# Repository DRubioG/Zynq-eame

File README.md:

# Introducción / Introduction

**[ES]** Este es el repositorio en GitHub del blog [soceame.wordpress.com](http://soceame.wordpress.com) en el que se colgará toda la información sobre cómo construir SoCs de Xilinx 

**[EN]** This is the GitHub's repository of the [soceame.wordpress.com](https://soceame.wordpress.com)'s blog where it will be uploaded all information about how to build Xilinx's SoCs

# Contenido / Content

- [Documentación/Documentation](/Documentacion): 

**[ES]** En esta carpeta se ubicarán los documentos que explican la construcción de los SoCs 

**[EN]** In this folder will be placed the documents which explaining how to build the SoCs

- [Zynq-eame_0](/Zynq-eame_0): ❗ No terminada / Unfinished ❗

**[ES]** Esta carpeta contiene los esquemáticos de la Zynq-eame_0 en pdf y en KiCad.

Esta placa está construida a partir de un XC7Z010-CLG400.

**[EN]** This folder contains the Zynq-eame_0' schematics in pdf and in KiCad.

This board is built from a XC7Z010-CLG400.

- [Zynq-eame_UltraScale_0](/Zynq-eame_UltraScale_0): ❗ Inicio / Started ❗

**[ES]** Esta carpeta contiene los esquemáticos de la Zynq-eame_UltraScale_0 en pdf y en KiCad.

Esta placa está construida a partir de un XCZU2CG-SBVA484.

**[EN]** This folder contains the Zynq-eame_UltraScale_0' schematics in pdf and in KiCad.

This board is built from a XCZU2CG-SBVA484.

**[ES]** Estos son proyectos Open Hardware 

**[EN]** These are Open Hardware projects

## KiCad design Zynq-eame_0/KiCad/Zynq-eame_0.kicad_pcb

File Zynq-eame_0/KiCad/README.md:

# FPGA_propia
 En este repositorio se subirán los ficheros que permitirán crear una FPGA basada en Zynq-7000

Todo el desarrollo está hecho con KiCad (software libre) para que cualquiera pueda replicarla o mejorarla a su gusto con los ficheros que se van a publicar

## Libreria
El fichero tiene una librería llamada 'Zynq-7000' en la que está el symbol de un XC7Z010 del cual se implementará la versión CLG400 (400 pines en formato de soldadura BGA) 
## XC7Z010-BUENO
El símbolo consta de 9 partes, de las que se va a describir su selección a continuación
### - _Símbolo A_

En este símbolo se reflejan los pines de referencia, además de los pines de depuración TMS, TCK, TDI y TDO. Estos pines pueden necesitar de un cable depurar para cargar el programa o de un USB OTG, que permita evitar tener que usar un cable depurador.

### - _Símbolo B_

En este símbolo se reflejan los pines que no tienen conexión

### - _Símbolo c_

En este símbolo se reflejan los pines de entrada/salida que se podrán configurar como se quiera

### - _Símbolo D_

En este símbolo se reflejan los pines de entrada/salida que se podrán configurar como se quiera

### - _Símbolo E_

En este símbolo se reflejan los pines que van a ir a la/las memoria ram. A los pines de la ram se pueden unir varias memorias para aumentar su tamaño.

### - _Símbolo F_

En este símbolo se reflejan los pines MIO

### - _Símbolo G_

En este símbolo se reflejan los pines MIO continuación de los anteriores

### - _Símbolo H_

En este símbolo se reflejan las alimentaciones de cada parte del integrado. Hay que tener en cuenta que cada parte tiene una alimentación distinta, la VCCO_BRAM y los VCCO_PINT de 1V, los VCCO_MIO 3.3V, los VCCO_DDR de 1.35V y los VCCAUX y los VCCPAUX de 1.8V

### - _Símbolo I_

En este símbolo se reflejan las masas de todo el integrado. Todas las masas van unidas a mismo punto.

### - *Formato del integrado*

En esta imagen se refleja como es el integrado CLG400 de 400 pines(20x20) para BGA

*** Toda la documentación del frabicante se puede obtener del siguiente enlace: ***
Documentación para el empaquetado: https://www.xilinx.com/support/documentation/user_guides/ug865-Zynq-7000-Pkg-Pinout.pdf
Documentación de los pines: https://www.xilinx.com/support/packagefiles/z7packages/xc7z010clg400pkg.txt

## Memoria RAM
Para la memoria ram se utiliza una MT4K256M16TW-107:P
### Datasheet
http://www.farnell.com/datasheets/3151560.pdf
### Símbolo
El símbolo utilizado es el siguiente

### Huella
La huella de la memoria ram consta de una matriz de 6x16 que está fragmetada en dos partes separadas por una zona en la que van 3 columnas de pines vacías.

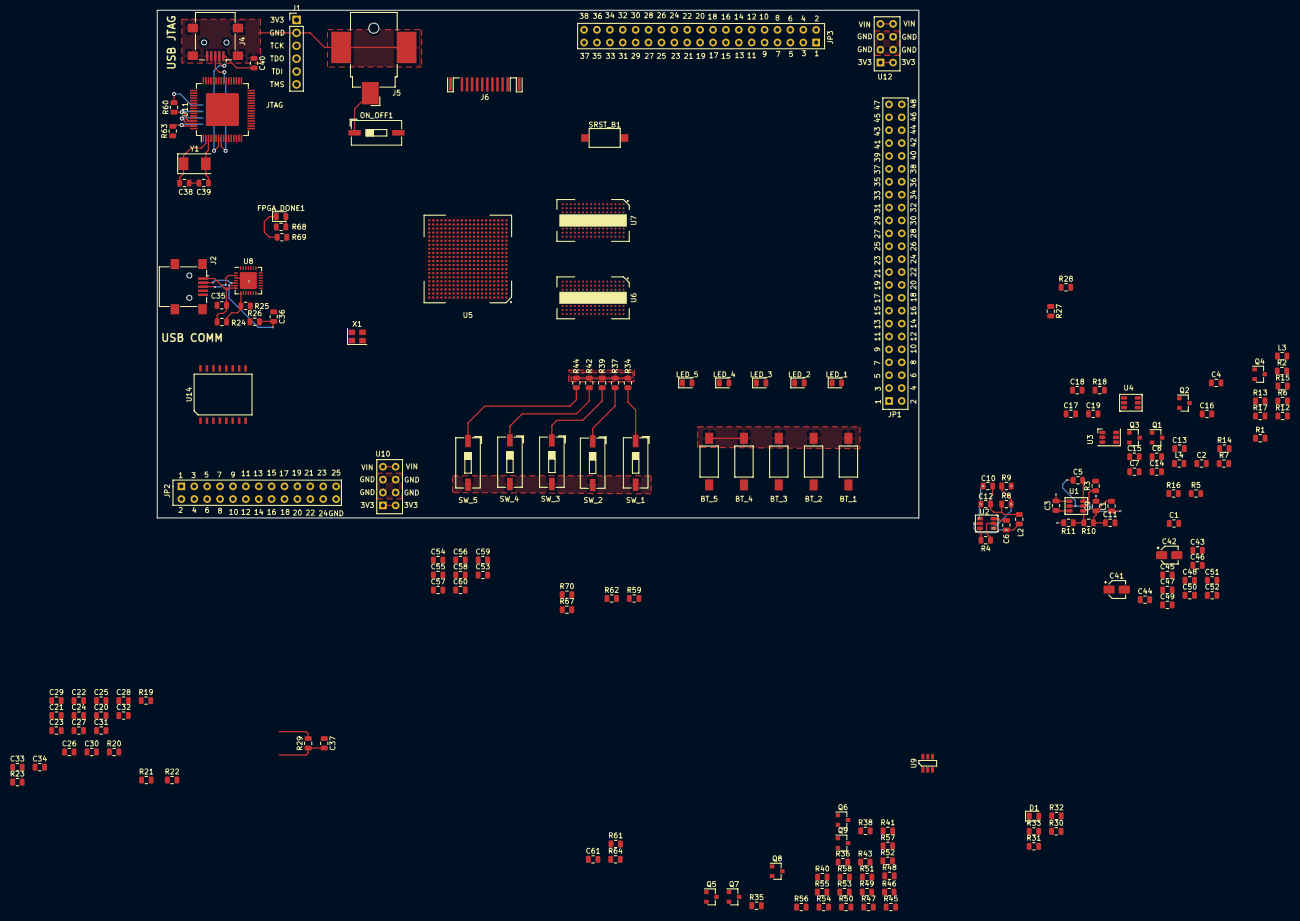
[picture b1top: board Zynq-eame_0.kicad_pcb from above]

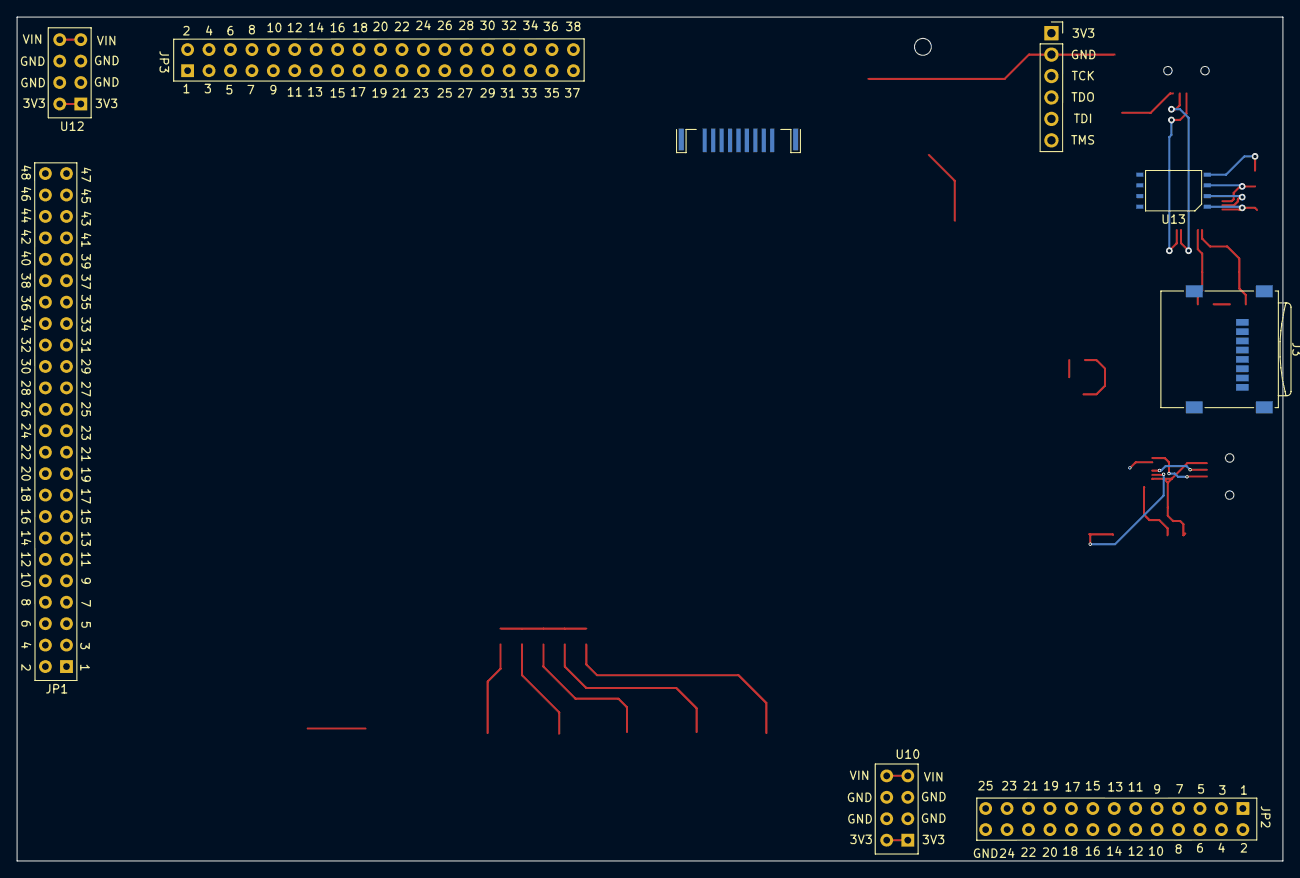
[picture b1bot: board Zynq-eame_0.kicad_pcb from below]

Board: 4 copper layers, 150.0 x 100.0 mm, 186 parts (2 on the bottom side), 302 nets.

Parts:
BT_1, BT_2, BT_3, BT_4, BT_5: SW_Push; SW_SPST_FSMSM
C1, C2, C3, C4, C9, C10, C11, C12, C13, C14, C15, C16: 10uF; C_0805_2012Metric
C5, C6, C7, C8, C17, C18, C19, C20, C21, C22, C23, C24, C25, C26, C27, C28, C29, C30, C31, C32, C33, C34, C37, C40, C43, C44, C53, C54, C55, C56, C57, C58, C59, C60, C61: 100nF; C_0805_2012Metric
C35: 4.7uF; R_0805_2012Metric
C36: 100nF; R_0805_2012Metric
C38, C39: 27pF; C_0805_2012Metric
C41, C42: 4.7uF; CP_Elec_3x5.4
C45: 3.3uF; C_0805_2012Metric
C46, C47, C48, C49, C50, C51, C52: C; C_0805_2012Metric
D1: LED_ALT; D_0805_2012Metric
FPGA_DONE1: LED_ALT; LED_0805_2012Metric
J1: Conn_01x06; PinHeader_1x06_P2.54mm_Vertical
J2, J4: USB_B_Micro; USB_Mini-B_Lumberg_2486_01_Horizontal
J3: Micro_SD_Card; microSD_HC_Wuerth_693072010801
J5: Barrel_Jack; BarrelJack_CUI_PJ-036AH-SMT_Horizontal
J6: HDMI_A; HDMI_A_Contact_Technology_HDMI-19APL2_Horizontal
JP1: PINES_48
JP2: PIN_25; PINES_40
JP3: PINES_38
L1, L2, L3, L4: 4.7uH; L_0805_2012Metric
LED_1, LED_2, LED_3, LED_4, LED_5: LED_ALT; LED_0805_2012Metric
ON_OFF1: SW_SPST; SW_DIP_SPSTx01_Slide_9.78x4.72mm_W8.61mm_P2.54mm
Q1, Q2, Q3, Q4: MMBT3904; SOT-23
Q5, Q6, Q7, Q8, Q9: MMBF170; SOT-23
R1, R2, R4, R5, R6, R7, R25, R36, R41, R46, R51, R56: 10k; R_0805_2012Metric
R3, R16, R17: 0R; R_0805_2012Metric
R8, R12: 33k; R_0805_2012Metric
R9, R11, R13, R14: 100k; R_0805_2012Metric
R10: 79k; R_0805_2012Metric
R15: 75k; R_0805_2012Metric
R18, R23: 240R 1%; R_0805_2012Metric
R19, R20, R21, R22: 1k 1%; R_0805_2012Metric
R24, R29: 4.7k; R_0805_2012Metric
R26, R35, R40, R45, R50, R55: 1k; R_0805_2012Metric
R27, R28, R34, R37, R39, R42, R44, R47, R49, R52, R54, R57, R67: 4.7K; R_0805_2012Metric
R30: 820; R_0805_2012Metric
R31: 1300; R_0805_2012Metric
R32, R64, R68, R69: 1K; R_0805_2012Metric
R33, R59, R62, R63: 10K; R_0805_2012Metric
R38, R43, R48, R53, R58: 261; R_0805_2012Metric
R60: 2K2; R_0805_2012Metric
R61: 12K; R_0805_2012Metric
R70: 330; R_0805_2012Metric
SRST_B1: SW_Push; SW_SPST_CK_RS282G05A3
SW_1, SW_2, SW_3, SW_4, SW_5: SW_SPST; SW_DIP_SPSTx01_Slide_9.78x4.72mm_W8.61mm_P2.54mm
U1, U2, U3, U4: TPS563201
U5: XC7Z010-BUENO; BGA-400_20x20_17.0x17.0mm
U6, U7: MT41K256M16TW-107_P; BGA-144_9x16_8.0x14.0mm
U8: CP2102N-A01-GQFN28; QFN-28-1EP_5x5mm_P0.5mm_EP3.35x3.35mm
U9: TPS3106K33DBV; SOT-23
U10, U12: PINES_ALIMENTACION; PINES_40
U11: FT2232H; LQFP-64-1EP_10x10mm_P0.5mm_EP6.5x6.5mm
U13: 93C46; EIAJ_SOIC
U14: S25FL128S; S03016-(SOIC-16)
X1: ASE-33.333MHz; Oscillator_SMD_Abracon_ASE-4Pin_3.2x2.5mm
Y1: 12MHz; Crystal_SMD_0603-2Pin_6.0x3.5mm

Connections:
+1V0: C10.1, C12.1, L2.2, Q2.1, R8.1, R30.1, U5.G7, U5.G11, U5.G13, U5.H10, U5.H12, U5.J7, U5.J13, U5.K12, U5.L7, U5.L13, U5.M12, U5.N7, U5.N13, U5.P8, U5.P12, U5.R7, U5.R13
+1V8: C14.1, C16.1, C45.1, C46.1, C47.1, C48.1, C49.1, C50.1, C51.1, C52.1, L4.2, R3.2, R14.1, U5.F8, U5.F11, U5.G8, U5.G9, U5.H8, U5.J9, U5.J11, U5.K8, U5.L11, U5.M8, U5.N9, U5.N11, U5.P10, U5.R9, U11.12, U11.37, U11.49, U11.64
+1V35: C9.1, C11.1, C20.1, C21.1, C23.1, C24.1, C25.1, C26.1, C27.1, C28.1, C29.1, C30.1, C53.1, C54.1, C55.1, C56.1, C57.1, C58.1, C59.1, L1.2, R1.2, R10.1, R19.1, U5.A3, U5.D2, U5.E5, U5.G1, U5.H4, U5.L3, U5.P2, U5.R5, U5.U1, U5.V4, U6.A1, U6.A8, U6.B2, U6.C1, U6.C9, U6.D2, U6.D9, U6.E9, U6.F1, U6.G7, U6.H2, U6.H9, U6.K2, U6.K8, U6.N1, U6.N9, U6.R1, U6.R9, U7.A1, U7.A8, U7.B2, U7.C1, U7.C9, U7.D2, U7.D9, U7.E9, U7.F1, U7.G7, U7.H2, U7.H9, U7.K2, U7.K8, U7.N1, U7.N9, U7.R1, U7.R9
+3V3: BT_1.2, BT_2.2, BT_3.2, BT_4.2, BT_5.2, C13.1, C15.1, C37.2, C61.1, J1.1, J3.4, L3.2, LED_1.2, LED_2.2, LED_3.2, LED_4.2, LED_5.2, R12.1, R16.1, R17.1, R27.1, R28.1, R29.1, R32.2, R33.1, R34.1, R37.1, R39.1, R42.1, R44.1, R59.1, R62.1, R63.1, R64.1, R67.1, R68.1, R70.1, U5.A13, U5.B6, U5.B16, U5.C19, U5.D7, U5.D12, U5.E15, U5.F18, U5.H14, U5.J17, U5.K6, U5.K20, U5.M6, U5.M16, U5.N6, U5.R6, U5.T6, U5.T8, U5.U11, U5.W7, U5.Y10, U9.6, U10.1, U10.2, U11.20, U11.31, U11.42, U11.50, U11.56, U12.1, U12.2, U13.6, U13.8, U14.2, X1.4
+5V: J5.1, ON_OFF1.1
/Entradas y Salidas/BANK34_N17: JP1.42, U5.N17
/Entradas y Salidas/BANK34_N18: JP1.2, U5.N18
/Entradas y Salidas/BANK34_N20: JP1.6, U5.N20
/Entradas y Salidas/BANK34_P14: JP1.21, U5.P14
/Entradas y Salidas/BANK34_P15: JP1.46, U5.P15
/Entradas y Salidas/BANK34_P16: JP1.48, U5.P16
/Entradas y Salidas/BANK34_P18: JP1.44, U5.P18
/Entradas y Salidas/BANK34_P19: JP1.4, U5.P19
/Entradas y Salidas/BANK34_P20: JP1.8, U5.P20
/Entradas y Salidas/BANK34_R14: JP1.23, U5.R14
/Entradas y Salidas/BANK34_R16: JP1.26, U5.R16
/Entradas y Salidas/BANK34_R17: JP1.28, U5.R17
/Entradas y Salidas/BANK34_R18: JP1.32, U5.R18
/Entradas y Salidas/BANK34_R19: JP1.1, U5.R19
/Entradas y Salidas/BANK34_T10: JP1.5, U5.T10
/Entradas y Salidas/BANK34_T11: JP1.3, U5.T11
/Entradas y Salidas/BANK34_T12: JP1.7, U5.T12
/Entradas y Salidas/BANK34_T14: JP1.17, U5.T14
/Entradas y Salidas/BANK34_T15: JP1.19, U5.T15
/Entradas y Salidas/BANK34_T16: JP1.33, U5.T16
/Entradas y Salidas/BANK34_T17: JP1.30, U5.T17
/Entradas y Salidas/BANK34_T20: JP1.10, U5.T20
/Entradas y Salidas/BANK34_U12: JP1.9, U5.U12
/Entradas y Salidas/BANK34_U14: JP1.41, U5.U14
/Entradas y Salidas/BANK34_U15: JP1.43, U5.U15
/Entradas y Salidas/BANK34_U17: JP1.35, U5.U17
/Entradas y Salidas/BANK34_U18: JP1.45, U5.U18
/Entradas y Salidas/BANK34_U19: JP1.47, U5.U19
/Entradas y Salidas/BANK34_U20: JP1.12, U5.U20
/Entradas y Salidas/BANK34_V12: JP1.13, U5.V12
/Entradas y Salidas/BANK34_V13: JP1.11, U5.V13
/Entradas y Salidas/BANK34_V15: JP1.37, U5.V15
/Entradas y Salidas/BANK34_V16: JP1.22, U5.V16
/Entradas y Salidas/BANK34_V17: JP1.34, U5.V17
/Entradas y Salidas/BANK34_V18: JP1.36, U5.V18
/Entradas y Salidas/BANK34_V20: JP1.14, U5.V20
/Entradas y Salidas/BANK34_W13: JP1.15, U5.W13
/Entradas y Salidas/BANK34_W14: JP1.29, U5.W14
/Entradas y Salidas/BANK34_W15: JP1.39, U5.W15
/Entradas y Salidas/BANK34_W16: JP1.24, U5.W16
/Entradas y Salidas/BANK34_W18: JP1.38, U5.W18
/Entradas y Salidas/BANK34_W19: JP1.40, U5.W19
/Entradas y Salidas/BANK34_W20: JP1.16, U5.W20
/Entradas y Salidas/BANK34_Y14: JP1.31, U5.Y14
/Entradas y Salidas/BANK34_Y16: JP1.25, U5.Y16
/Entradas y Salidas/BANK34_Y17: JP1.27, U5.Y17
/Entradas y Salidas/BANK34_Y18: JP1.18, U5.Y18
/Entradas y Salidas/BANK34_Y19: JP1.20, U5.Y19
/Entradas y Salidas/BANK35_F16: JP2.3, U5.F16
/Entradas y Salidas/BANK35_F17: JP2.5, U5.F17
/Entradas y Salidas/BANK35_G14: JP2.1, U5.G14
/Entradas y Salidas/BANK35_G15: JP2.18, U5.G15
/Entradas y Salidas/BANK35_G19: JP2.12, U5.G19
/Entradas y Salidas/BANK35_G20: JP2.14, U5.G20
/Entradas y Salidas/BANK35_H15: JP2.16, U5.H15
/Entradas y Salidas/BANK35_H20: JP2.10, U5.H20
/Entradas y Salidas/BANK35_J14: JP2.22, U5.J14
/Entradas y Salidas/BANK35_J15: JP2.6, U5.J15
/Entradas y Salidas/BANK35_J16: JP2.4, U5.J16
/Entradas y Salidas/BANK35_J20: JP2.8, U5.J20
/Entradas y Salidas/BANK35_K14: JP2.20, U5.K14
/Entradas y Salidas/BANK35_K16: JP2.2, U5.K16
/Entradas y Salidas/BANK35_L14: JP2.23, U5.L14
/Entradas y Salidas/BANK35_L15: JP2.21, U5.L15
/Entradas y Salidas/BANK35_L19: JP2.15, U5.L19
/Entradas y Salidas/BANK35_M14: JP2.19, U5.M14
/Entradas y Salidas/BANK35_M15: JP2.17, U5.M15
/Entradas y Salidas/BANK35_M17: JP2.11, U5.M17
/Entradas y Salidas/BANK35_M18: JP2.13, U5.M18
/Entradas y Salidas/BANK35_M19: JP2.7, U5.M19
/Entradas y Salidas/BANK35_M20: JP2.9, U5.M20
/Entradas y Salidas/BANK35_N15: JP2.24, U5.N15
/Entradas y Salidas/BANK35_N16: JP2.25, U5.N16
/Entradas y Salidas/BT_1: BT_1.1, R47.2, U5.H18
/Entradas y Salidas/BT_2: BT_2.1, R49.2, U5.F19
/Entradas y Salidas/BT_3: BT_3.1, R52.2, U5.F20
/Entradas y Salidas/BT_4: BT_4.1, R54.2, U5.G17
/Entradas y Salidas/BT_5: BT_5.1, R57.2, U5.G18
/Entradas y Salidas/HDMI_CLK+: J6.10, U5.B19
/Entradas y Salidas/HDMI_CLK-: J6.12, U5.A20
/Entradas y Salidas/HDMI_D0+: J6.7, U5.E17
/Entradas y Salidas/HDMI_D0-: J6.9, U5.D18
/Entradas y Salidas/HDMI_D1+: J6.4, U5.D19
/Entradas y Salidas/HDMI_D1-: J6.6, U5.D20
/Entradas y Salidas/HDMI_D2+: J6.1, U5.E18
/Entradas y Salidas/HDMI_D2-: J6.3, U5.E19
/Entradas y Salidas/LED_1: R35.1, U5.L20
/Entradas y Salidas/LED_2: R40.1, U5.K19
/Entradas y Salidas/LED_3: R45.1, U5.J19
/Entradas y Salidas/LED_4: R50.1, U5.L16
/Entradas y Salidas/LED_5: R55.1, U5.L17
/Entradas y Salidas/SW_1: R34.2, SW_1.1, U5.K17
/Entradas y Salidas/SW_2: R37.2, SW_2.1, U5.K18
/Entradas y Salidas/SW_3: R39.2, SW_3.1, U5.H16
/Entradas y Salidas/SW_4: R42.2, SW_4.1, U5.H17
/Entradas y Salidas/SW_5: R44.2, SW_5.1, U5.J18
/Memoria RAM/DDR_A0: U5.N2, U6.N3, U7.N3
/Memoria RAM/DDR_A1: U5.K2, U6.P7, U7.P7
/Memoria RAM/DDR_A2: U5.M3, U6.P3, U7.P3
/Memoria RAM/DDR_A3: U5.K3, U6.N2, U7.N2
/Memoria RAM/DDR_A4: U5.M4, U6.P8, U7.P8
/Memoria RAM/DDR_A5: U5.L1, U6.P2, U7.P2
/Memoria RAM/DDR_A6: U5.L4, U6.R8, U7.R8
/Memoria RAM/DDR_A7: U5.K4, U6.R2, U7.R2
/Memoria RAM/DDR_A8: U5.K1, U6.T8, U7.T8
/Memoria RAM/DDR_A9: U5.J4, U6.R3, U7.R3
/Memoria RAM/DDR_A10: U5.F5, U6.L7, U7.L7
/Memoria RAM/DDR_A11: U5.G4, U6.R7, U7.R7
/Memoria RAM/DDR_A12: U5.E4, U6.N7, U7.N7
/Memoria RAM/DDR_A13: U5.D4, U6.T3, U7.T3
/Memoria RAM/DDR_A14: U5.F4, U6.T7, U7.T7
/Memoria RAM/DDR_BA0: U5.L5, U6.M2, U7.M2
/Memoria RAM/DDR_BA1: U5.R4, U6.N8, U7.N8
/Memoria RAM/DDR_BA2: U5.J5, U6.M3, U7.M3
/Memoria RAM/DDR_CAS: U5.P5, U6.K3, U7.K3
/Memoria RAM/DDR_CKE: U5.N3, U6.K9, U7.K9
/Memoria RAM/DDR_CLK+: R21.1, U5.L2, U6.J7, U7.J7
/Memoria RAM/DDR_CLK-: R21.2, U5.M2, U6.K7, U7.K7
/Memoria RAM/DDR_CS: U5.N1, U6.L2, U7.L2
/Memoria RAM/DDR_D0: U5.C3, U6.E3
/Memoria RAM/DDR_D1: U5.B3, U6.F7
/Memoria RAM/DDR_D2: U5.A2, U6.F2, U6.F8
/Memoria RAM/DDR_D4: U5.D3, U6.H3
/Memoria RAM/DDR_D5: U5.D1, U6.H8
/Memoria RAM/DDR_D6: U5.C1, U6.G2
/Memoria RAM/DDR_D7: U5.E1, U6.H7
/Memoria RAM/DDR_D8: U5.E2, U6.D7
/Memoria RAM/DDR_D9: U5.E3, U6.C3
/Memoria RAM/DDR_D10: U5.G3, U6.C8
/Memoria RAM/DDR_D11: U5.H3, U6.C2
/Memoria RAM/DDR_D12: U5.J3, U6.A7
/Memoria RAM/DDR_D13: U5.H2, U6.A2
/Memoria RAM/DDR_D14: U5.H1, U6.B8
/Memoria RAM/DDR_D15: U5.J1, U6.A3
/Memoria RAM/DDR_D16: U5.P1, U7.E3
/Memoria RAM/DDR_D17: U5.P3, U7.F7
/Memoria RAM/DDR_D18: U5.R3, U7.F2
/Memoria RAM/DDR_D19: U5.R1, U7.F8
/Memoria RAM/DDR_D20: U5.T4, U7.H3
/Memoria RAM/DDR_D21: U5.U4, U7.H8
/Memoria RAM/DDR_D22: U5.U2, U7.G2
/Memoria RAM/DDR_D23: U5.U3, U7.H7
/Memoria RAM/DDR_D24: U5.V1, U7.D7
/Memoria RAM/DDR_D25: U5.Y3, U7.C3
/Memoria RAM/DDR_D26: U5.W1, U7.C8
/Memoria RAM/DDR_D27: U5.Y4, U7.C2
/Memoria RAM/DDR_D28: U5.Y2, U7.A7
/Memoria RAM/DDR_D29: U5.W3, U7.A2
/Memoria RAM/DDR_D30: U5.V2, U7.B8
/Memoria RAM/DDR_D31: U5.V3, U7.A3
/Memoria RAM/DDR_DQM0: U5.A1, U6.E7
/Memoria RAM/DDR_DQM1: U5.F1, U6.D3
/Memoria RAM/DDR_DQM2: U5.T1, U7.E7
/Memoria RAM/DDR_DQM3: U5.Y1, U7.D3
/Memoria RAM/DDR_DQS0+: U5.C2, U6.F3
/Memoria RAM/DDR_DQS0-: U5.B2, U6.G3
/Memoria RAM/DDR_DQS1+: U5.G2, U6.C7
/Memoria RAM/DDR_DQS1-: U5.F2, U6.B7
/Memoria RAM/DDR_DQS2+: U5.R2, U7.F3
/Memoria RAM/DDR_DQS2-: U5.T2, U7.G3
/Memoria RAM/DDR_DQS3+: U5.W5, U7.C7
/Memoria RAM/DDR_DQS3-: U5.W4, U7.B7
/Memoria RAM/DDR_ODT: U5.N5, U6.K1, U7.K1
/Memoria RAM/DDR_RAS: U5.P4, U6.J3, U7.J3
/Memoria RAM/DDR_RESETN: R22.1, U5.B4, U6.T2, U7.T2
/Memoria RAM/DDR_VREF: C17.1, C21.2, C22.1, R19.2, R20.1, U5.H6, U5.P6
/Memoria RAM/DDR_WE: U6.L3, U7.L3
/Referencias y MIOs/EECLK: R62.2, U11.62, U13.2
/Referencias y MIOs/EECS: R63.2, U11.63, U13.1
/Referencias y MIOs/EEDATA: R60.1, U11.61, U13.3
/Referencias y MIOs/FPGA_DONE: FPGA_DONE1.2, R68.2, U5.R11
/Referencias y MIOs/MIO1: R70.2, U5.A7, U14.7
/Referencias y MIOs/MIO2: U5.B8, U14.15
/Referencias y MIOs/MIO3: U5.D6, U14.8
/Referencias y MIOs/MIO4: U5.B7, U14.9
/Referencias y MIOs/MIO5: U5.A6, U14.1
/Referencias y MIOs/MIO6: U5.A5, U14.16
/Referencias y MIOs/PS_CLK: U5.E7, X1.3
/Referencias y MIOs/RX(MIO24): U5.A16, U8.26
/Referencias y MIOs/SD_CLK: J3.5, U5.D14
/Referencias y MIOs/SD_CMD: J3.3, U5.C17
/Referencias y MIOs/SD_D0: J3.7, U5.E12
/Referencias y MIOs/SD_D1: J3.8, U5.A9
/Referencias y MIOs/SD_D2: J3.1, U5.F13
/Referencias y MIOs/SD_D3: J3.2, U5.B15
/Referencias y MIOs/SRST_B: R67.2, SRST_B1.1, U5.B10
/Referencias y MIOs/TCK: J1.3, U5.F9, U11.16
/Referencias y MIOs/TDI: J1.5, U5.G6, U11.17
/Referencias y MIOs/TDO: J1.4, U5.F6, U11.18
/Referencias y MIOs/TMS: J1.6, U5.J6, U11.19
/Referencias y MIOs/TX(MIO25): U5.F15, U8.25
GND: C1.2, C2.2, C3.2, C4.2, C9.2, C10.2, C11.2, C12.2, C13.2, C14.2, C15.2, C16.2, C17.2, C18.2, C19.2, C20.2, C22.2, C23.2, C24.2, C25.2, C26.2, C27.2, C28.2, C29.2, C30.2, C31.2, C32.2, C33.2, C34.2, C35.1, C36.1, C37.1, C38.2, C39.2, C40.1, C41.2, C42.2, C43.2, C44.2, C45.2, C46.2, C47.2, C48.2, C49.2, C50.2, C51.2, C52.2, C53.2, C54.2, C55.2, C56.2, C57.2, C58.2, C59.2, C61.2, D1.1, J1.2, J2.5, J2.6, J3.6, J3.9, J4.5, J4.6, J5.2, J6.2, J6.5, J6.8, J6.11, J6.17, J6.SH, JP2.26, Q1.2, Q2.2, Q3.2, Q4.2, Q5.2, Q6.2, Q7.2, Q8.2, Q9.2, R9.2, R11.2, R13.2, R15.2, R18.2, R20.2, R22.2, R23.2, R25.2, R31.2, R36.2, R41.2, R46.2, R47.1, R49.1, R51.2, R52.1, R54.1, R56.2, R57.1, R61.1, R69.2, SRST_B1.2, SW_1.2, SW_2.2, SW_3.2, SW_4.2, SW_5.2, U1.1, U2.1, U3.1, U4.1, U5.A8, U5.A18, U5.B1, U5.B11, U5.C4, U5.C9, U5.C14, U5.D17, U5.E10, U5.E20, U5.F3, U5.F7, U5.F10, U5.G10, U5.G12, U5.G16, U5.H7, U5.H9, U5.H11, U5.H13, U5.H19, U5.J2, U5.J8, U5.J10, U5.J12, U5.K5, U5.K7, U5.K9, U5.K10, U5.K11, U5.K13, U5.K15, U5.L8, U5.L9, U5.L10, U5.L12, U5.L18, U5.M1, U5.M7, U5.M9, U5.M10, U5.M11, U5.M13, U5.N4, U5.N8, U5.N10, U5.N12, U5.N14, U5.P7, U5.P9, U5.P11, U5.P13, U5.P17, U5.R8, U5.R12, U5.R20, U5.T3, U5.T7, U5.T13, U5.U6, U5.U13, U5.U16, U5.V9, U5.V19, U5.W2, U5.W12, U5.Y5, U5.Y15, U6.A9, U6.B1, U6.B3, U6.B9, U6.D1, U6.D8, U6.E1, U6.E2, U6.E8, U6.F9, U6.G1, U6.G8, U6.G9, U6.J2, U6.J8, U6.M1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
MIO_0: JP3.1, U5.E6
MIO_7: JP3.2, U5.D8
MIO_8: JP3.3, U5.D5
MIO_9: JP3.4, U5.B5
MIO_10: JP3.5, U5.E9
MIO_11: JP3.6, U5.C6
MIO_12: JP3.7, U5.D9
MIO_13: JP3.8, U5.E8
MIO_14: JP3.9, U5.C5
MIO_15: JP3.10, U5.C8
MIO_16: JP3.11, U5.A19
MIO_17: JP3.12, U5.E14
MIO_18: JP3.13, U5.B18
MIO_19: JP3.14, U5.D10
MIO_20: JP3.15, U5.A17
MIO_21: JP3.16, U5.F14
MIO_22: JP3.17, U5.B17
MIO_23: JP3.18, U5.D11
MIO_26: JP3.19, U5.A15
MIO_27: JP3.20, U5.D13
MIO_28: JP3.21, U5.C16
MIO_29: JP3.22, U5.C13
MIO_30: JP3.23, U5.C15
MIO_31: JP3.24, U5.E16
MIO_32: JP3.25, U5.A14
MIO_33: JP3.26, U5.D15
MIO_34: JP3.27, U5.A12
MIO_35: JP3.28, U5.F12
MIO_38: JP3.29, U5.E13
MIO_39: JP3.30, U5.C18
MIO_46: JP3.31, U5.D16
MIO_47: JP3.32, U5.B14
MIO_48: JP3.33, U5.B12
MIO_49: JP3.34, U5.C12
MIO_50: JP3.35, U5.B13
MIO_51: JP3.36, U5.B9
MIO_52: JP3.37, U5.C10
MIO_53: JP3.38, U5.C11
unnamed: C5.1, L1.1, U1.2
unnamed: C5.2, U1.6
unnamed: C6.1, L2.1, U2.2
unnamed: C6.2, U2.6
unnamed: C7.1, L3.1, U3.2
unnamed: C7.2, U3.6
unnamed: C8.1, L4.1, U4.2
unnamed: C8.2, U4.6
unnamed: C18.1, U6.M8
unnamed: C19.1, U6.H1
unnamed: C31.1, U5.H5
unnamed: C32.1, U5.G5
unnamed: C33.1, U7.M8
unnamed: C34.1, U7.H1
unnamed: C35.2, J2.1, R24.1, U8.7
unnamed: C36.2, R26.2, U8.6
unnamed: C38.1, U11.2, Y1.1
unnamed: C39.1, U11.3, Y1.2
unnamed: C40.2, J4.1
unnamed: C41.1, C43.1, U11.9
unnamed: C42.1, C44.1, U11.4
unnamed: D1.2, R32.1
unnamed: FPGA_DONE1.1, R69.1
unnamed: J2.2, U8.5
unnamed: J2.3, U8.4
unnamed: J4.2, U11.7
unnamed: J4.3, U11.8
unnamed: LED_1.1, R38.1
unnamed: LED_2.1, R43.1
unnamed: LED_3.1, R48.1
unnamed: LED_4.1, R53.1
unnamed: LED_5.1, R58.1
unnamed: Q1.1, R1.1
unnamed: Q1.3, Q3.1, R2.1
unnamed: Q2.3, Q4.1, R5.1
unnamed: Q3.3, R6.1, U3.5
unnamed: Q4.3, R7.1, U4.5
unnamed: Q5.1, R35.2, R36.1
unnamed: Q5.3, R38.2
unnamed: Q6.1, R40.2, R41.1
unnamed: Q6.3, R43.2
unnamed: Q7.1, R45.2, R46.1
unnamed: Q7.3, R48.2
unnamed: Q8.1, R50.2, R51.1
unnamed: Q8.3, R53.2
unnamed: Q9.1, R55.2, R56.1
unnamed: Q9.3, R58.2
unnamed: R3.1, U1.5
unnamed: R4.1, U2.5
unnamed: R8.2, R9.1, U2.4
unnamed: R10.2, R11.1, U1.4
unnamed: R12.2, R13.1, U3.4
unnamed: R14.2, R15.1, U4.4
unnamed: R18.1, U6.L8
unnamed: R23.1, U7.L8
unnamed: R24.2, R25.1, U8.8
unnamed: R26.1, U8.9
unnamed: R27.2, U5.R10
unnamed: R28.2, U5.L6
unnamed: R29.2, X1.1
unnamed: R30.2, R31.1, U9.4
unnamed: R59.2, R60.2, U13.4
unnamed: R61.2, U11.6
unnamed: R64.2, U11.14
PS_POR_B: R33.2, U5.C7, U9.1, U9.5
VCC: J6.18, R16.2, R17.2, U5.N19, U5.R15, U5.T18, U5.V14, U5.W17, U5.Y20
VCC_5V: C1.1, C2.1, C3.1, C4.1, ON_OFF1.2, R2.2, R4.2, R5.2, R6.2, R7.2, U1.3, U2.3, U3.3, U4.3, U10.7, U10.8, U12.7, U12.8

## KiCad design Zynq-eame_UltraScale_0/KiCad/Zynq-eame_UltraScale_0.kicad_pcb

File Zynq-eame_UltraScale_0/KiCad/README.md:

# FPGA_propia
 En este repositorio se subirán los ficheros que permitirán crear una FPGA basada en Zynq-7000

Todo el desarrollo está hecho con KiCad (software libre) para que cualquiera pueda replicarla o mejorarla a su gusto con los ficheros que se van a publicar

## Libreria
El fichero tiene una librería llamada 'Zynq-7000' en la que está el symbol de un XC7Z010 del cual se implementará la versión CLG400 (400 pines en formato de soldadura BGA) 
## XC7Z010-BUENO
El símbolo consta de 9 partes, de las que se va a describir su selección a continuación
### - _Símbolo A_

En este símbolo se reflejan los pines de referencia, además de los pines de depuración TMS, TCK, TDI y TDO. Estos pines pueden necesitar de un cable depurar para cargar el programa o de un USB OTG, que permita evitar tener que usar un cable depurador.

### - _Símbolo B_

En este símbolo se reflejan los pines que no tienen conexión

### - _Símbolo c_

En este símbolo se reflejan los pines de entrada/salida que se podrán configurar como se quiera

### - _Símbolo D_

En este símbolo se reflejan los pines de entrada/salida que se podrán configurar como se quiera

### - _Símbolo E_

En este símbolo se reflejan los pines que van a ir a la/las memoria ram. A los pines de la ram se pueden unir varias memorias para aumentar su tamaño.

### - _Símbolo F_

En este símbolo se reflejan los pines MIO

### - _Símbolo G_

En este símbolo se reflejan los pines MIO continuación de los anteriores

### - _Símbolo H_

En este símbolo se reflejan las alimentaciones de cada parte del integrado. Hay que tener en cuenta que cada parte tiene una alimentación distinta, la VCCO_BRAM y los VCCO_PINT de 1V, los VCCO_MIO 3.3V, los VCCO_DDR de 1.35V y los VCCAUX y los VCCPAUX de 1.8V

### - _Símbolo I_

En este símbolo se reflejan las masas de todo el integrado. Todas las masas van unidas a mismo punto.

### - *Formato del integrado*

En esta imagen se refleja como es el integrado CLG400 de 400 pines(20x20) para BGA

*** Toda la documentación del frabicante se puede obtener del siguiente enlace: ***
Documentación para el empaquetado: https://www.xilinx.com/support/documentation/user_guides/ug865-Zynq-7000-Pkg-Pinout.pdf
Documentación de los pines: https://www.xilinx.com/support/packagefiles/z7packages/xc7z010clg400pkg.txt

## Memoria RAM
Para la memoria ram se utiliza una MT4K256M16TW-107:P
### Datasheet
http://www.farnell.com/datasheets/3151560.pdf
### Símbolo
El símbolo utilizado es el siguiente

### Huella
La huella de la memoria ram consta de una matriz de 6x16 que está fragmetada en dos partes separadas por una zona en la que van 3 columnas de pines vacías.

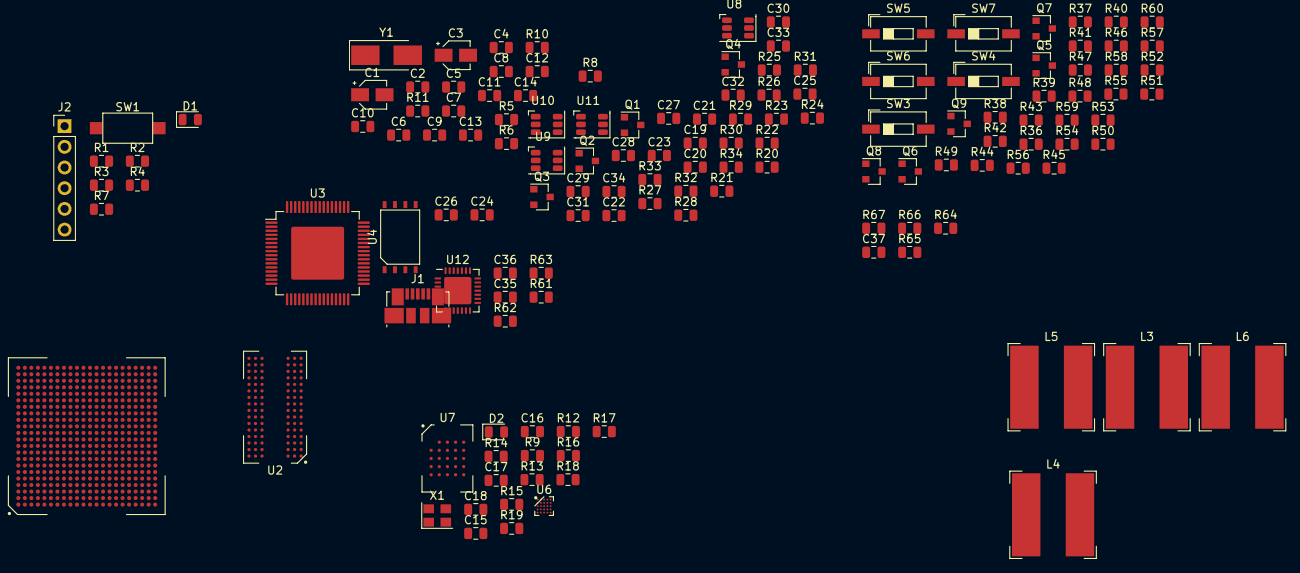
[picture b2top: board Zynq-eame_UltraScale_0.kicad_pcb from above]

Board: 2 copper layers, 139 parts (0 on the bottom side), 155 nets, no tracks yet.

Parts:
C1, C3: 4.7uF; CP_Elec_3x5.3
C2, C5, C6, C9, C10, C11, C12, C13, C14, C15, C16, C17, C18, C23, C24, C25, C26, C36, C37: 100nF; C_0805_2012Metric
C4, C7: 27pF; C_0805_2012Metric
C8: 3.3uF; C_0805_2012Metric
C19, C20, C21, C22, C27, C28, C29, C30, C31, C32, C33, C34: 10uF; C_0805_2012Metric
C35: 4.7uF; C_0805_2012Metric
D1, D2: LED_ALT; LED_0805_2012Metric
J1: USB_B_Micro; USB_Micro-B_Molex_47346-0001
J2: Conn_01x06; PinHeader_1x06_P2.54mm_Vertical
L3, L4, L5, L6: 4.7uH; L_Bourns-SRN1060
Q1, Q2, Q3, Q4: MMBT3904; SOT-23
Q5, Q6, Q7, Q8, Q9: MMBF170; SOT-23
R1, R2, R4, R16, R19, R37, R39, R40, R41, R44, R45, R46, R49, R50, R52, R54, R55, R56, R58, R60: 4.7K; R_0805_2012Metric
R3, R7, R12, R13, R36, R42, R47, R51, R57, R65: 1K; R_0805_2012Metric
R5, R9, R10, R17, R22, R23, R24, R62: 10k; R_0805_2012Metric
R6: 2k2; R_0805_2012Metric
R8: 12k; R_0805_2012Metric
R11, R63: 1k; R_0805_2012Metric
R14: 820; R_0805_2012Metric
R15: 1300; R_0805_2012Metric
R18: 330; R_0805_2012Metric
R20, R21, R26, R38, R43, R48, R53, R59: 10K; R_0805_2012Metric
R25: 0R; R_0805_2012Metric
R27, R30, R32, R34: 100k; R_0805_2012Metric
R28: 75k; R_0805_2012Metric
R29: 56k; R_0805_2012Metric
R31: 33k; R_0805_2012Metric
R33: 20K; R_0805_2012Metric
R61: 4.7k; R_0805_2012Metric
R64: 300; R_0805_2012Metric
R66, R67: 240; R_0805_2012Metric
SW1: SW_Push; SW_SPST_CK_RS282G05A3
SW3, SW4, SW5, SW6, SW7: SW_SPST; SW_DIP_SPSTx01_Slide_6.7x4.1mm_W6.73mm_P2.54mm_LowProfile_J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
U1: XCZU2CG; SBVA484
U2: MT40A512M16; FBGA96_LY
U3: FT2232H; LQFP-64-1EP_10x10mm_P0.5mm_EP6.5x6.5mm
U4: 93C46; EIAJ_SOIC
U6: IP4856CX25; BGA-25_5x5_2.049999x2.049999mm
U7: MT25QU512ABB; BGA-25_5x5_6.0x8.0mm
U8, U9, U10, U11: TPS563201
U12: CP2102N-A01-GQFN28; QFN-28-1EP_5x5mm_P0.5mm_EP3.35x3.35mm
X1: ASE-33.333MHz; Oscillator_SMD_Abracon_ASE-4Pin_3.2x2.5mm
Y1: 12MHz; Crystal_SMD_5032-2Pin_5.0x3.2mm_HandSoldering

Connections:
+0V85: C30.1, C34.1, L6.2, Q2.1, R33.1, U1.F19, U1.H7, U1.H8, U1.H10, U1.H19, U1.J7, U1.J9, U1.J11, U1.K8, U1.K19, U1.L7, U1.L11, U1.M7, U1.M8, U1.N7, U1.N11, U1.N12, U1.N13, U1.N14, U1.N17, U1.P8, U1.P10, U1.P12, U1.P13, U1.P17, U1.R6, U1.R7, U1.R9, U1.R11, U1.R13, U1.R14, U1.R15, U1.R16, U1.T6, U1.T12, U1.T13, U1.T14, U1.T16, U1.T17
+1V2: C28.1, C32.1, L4.2, R20.2, R29.2, U1.AB18, U1.M14, U1.M15, U1.P19, U1.T20, U1.V16, U1.V21, U1.Y17, U1.Y22, U2.A1, U2.A2, U2.A8, U2.A9, U2.C1, U2.C9, U2.D2, U2.D8, U2.D9, U2.E3, U2.E8, U2.F1, U2.F2, U2.F8, U2.G1, U2.G9, U2.H1, U2.H9, U2.J2, U2.J8
+1V8: C8.1, C9.1, C10.1, C11.1, C12.1, C13.1, C14.1, C15.1, C17.1, C27.2, C31.2, L3.2, R18.1, R25.1, R27.1, R37.1, R39.1, R41.1, R44.1, R46.1, U1.A21, U1.AA5, U1.B3, U1.B8, U1.B19, U1.C4, U1.C11, U1.C16, U1.D14, U1.D19, U1.E7, U1.F10, U1.G3, U1.G13, U1.H16, U1.J6, U1.K2, U1.K5, U1.K6, U1.L6, U1.L13, U1.L14, U1.L16, U1.L17, U1.M6, U1.M12, U1.M16, U1.M17, U1.M20, U1.P4, U1.P6, U1.V6, U3.12, U3.37, U3.49, U3.64, U6.B3, U7.B4
+2V5: R64.1, R65.2, U2.B1, U2.R9
+3V3: C16.1, C18.2, C29.1, C33.1, J2.6, L5.2, R1.2, R2.2, R3.2, R4.2, R5.1, R9.1, R10.1, R11.2, R12.2, R16.2, R17.1, R19.1, R31.1, R64.2, U3.20, U3.31, U3.42, U3.50, U3.56, U4.6, U4.8, U6.A4, U6.C4, X1.4
/DDR/DDR_A0: U1.AA22, U2.P3
/DDR/DDR_A1: U1.AB20, U2.P7
/DDR/DDR_A2: U1.AB17, U2.R3
/DDR/DDR_A3: U1.AB19, U2.N7
/DDR/DDR_A4: U1.AB21, U2.N3
/DDR/DDR_A5: U1.AB16, U2.P8
/DDR/DDR_A6: U1.Y20, U2.P2
/DDR/DDR_A7: U1.Y19, U2.R8
/DDR/DDR_A8: U1.W17, U2.R2
/DDR/DDR_A9: U1.Y18, U2.R7
/DDR/DDR_A10: U1.Y21, U2.M3
/DDR/DDR_A11: U1.AA21, U2.T2
/DDR/DDR_A12: U1.AA18, U2.M7
/DDR/DDR_A13: U1.AA19, U2.T8
/DDR/DDR_A14: U1.AA17, U2.L2
/DDR/DDR_A15: U1.AA16, U2.M8
/DDR/DDR_A16: U1.Y16, U2.L8
/DDR/DDR_ACTN: U1.U15, U2.L3
/DDR/DDR_ALERTN: U1.T21, U2.P9
/DDR/DDR_BA0: U1.U17, U2.N2
/DDR/DDR_BA1: U1.V17, U2.N8
/DDR/DDR_BG0: U1.U16, U2.M2
/DDR/DDR_CK: U1.V20, U2.K7
/DDR/DDR_CKE: U1.U22, U2.K2
/DDR/DDR_CK_N: U1.W20, U2.K8
/DDR/DDR_CS: U1.V22, U2.L7
/DDR/DDR_D0: U1.AB11, U2.G2
/DDR/DDR_D1: U1.Y10, U2.F7
/DDR/DDR_D2: U1.AB10, U2.H3
/DDR/DDR_D3: U1.W10, U2.H7
/DDR/DDR_D4: U1.AA8, U2.H2
/DDR/DDR_D5: U1.Y8, U2.H8
/DDR/DDR_D6: U1.AB7, U2.J3
/DDR/DDR_D7: U1.AA7, U2.J7
/DDR/DDR_D8: U1.AA11, U2.A3
/DDR/DDR_D9: U1.Y11, U2.B8
/DDR/DDR_D10: U1.AA12, U2.C3
/DDR/DDR_D11: U1.AB12, U2.C7
/DDR/DDR_D12: U1.Y14, U2.C2
/DDR/DDR_D13: U1.AA14, U2.C8
/DDR/DDR_D14: U1.Y15, U2.D3
/DDR/DDR_D15: U1.AB15, U2.D7
/DDR/DDR_DM0: U1.AB9, U2.E7
/DDR/DDR_DM1: U1.AB14, U2.E2
/DDR/DDR_DQS_N0: U1.AA9, U2.F3
/DDR/DDR_DQS_N1: U1.AA13, U2.A7
/DDR/DDR_DQS_P0: U1.Y9, U2.G3
/DDR/DDR_DQS_P1: U1.Y13, U2.B7
/DDR/DDR_ODT: U1.W22, U2.K3
/DDR/DDR_PARITY: U1.U19, U2.T3
/DDR/DDR_RESETN: U1.T18, U2.P1
/MIO&REFERENCE/EECLK: R9.2, U3.62, U4.2
/MIO&REFERENCE/EECS: R10.2, U3.63, U4.1
/MIO&REFERENCE/EEDATA: R6.1, U3.61, U4.3
/MIO&REFERENCE/MIO8_TX: U1.V3, U12.25
/MIO&REFERENCE/MIO9_RX: U1.V5, U12.26
/MIO&REFERENCE/MIO_SD1_CLK: U1.C13, U6.C1
/MIO&REFERENCE/MIO_SD1_CMD: U1.A13, U6.D2
/MIO&REFERENCE/MIO_SD1_DAT0: U1.C12, U6.D1
/MIO&REFERENCE/MIO_SD1_DAT1: U1.B12, U6.E1
/MIO&REFERENCE/MIO_SD1_DAT2: U1.D13, U6.A1
/MIO&REFERENCE/MIO_SD1_DAT3: U1.A12, U6.B1
/MIO&REFERENCE/MIO_SD1_DIR_CMD: U1.D11, U6.A2
/MIO&REFERENCE/MIO_SD1_DIR_DAT0: U1.B10, U6.A3
/MIO&REFERENCE/PS_CLK: U1.H14, X1.3
/MIO&REFERENCE/PS_DONE: D1.2, R3.1, U1.L12
/MIO&REFERENCE/PS_ERROR: D2.2, R12.1, U1.K16
/MIO&REFERENCE/PS_INIT_B: R1.1, U1.K15
/MIO&REFERENCE/PS_POR_B: R17.2, U1.K12
/MIO&REFERENCE/PS_PROG_B: R2.1, U1.K14
/MIO&REFERENCE/PS_TCK: J2.4, U1.H13, U3.16
/MIO&REFERENCE/PS_TDI: J2.2, U1.H12, U3.17
/MIO&REFERENCE/PS_TDO: J2.3, U1.J13, U3.18
/MIO&REFERENCE/PS_TMS: J2.1, U1.J12, U3.19
/MIO&REFERENCE/QSPI_CLK: U1.U4, U7.B2
/MIO&REFERENCE/QSPI_CS: R18.2, U1.AA1, U7.C2
/MIO&REFERENCE/QSPI_DQ0: U1.U6, U7.D3
/MIO&REFERENCE/QSPI_DQ1: U1.W1, U7.D2
/MIO&REFERENCE/QSPI_DQ2: U1.V2, U7.C4
/MIO&REFERENCE/QSPI_DQ3: U1.U5, U7.D4
/MIO&REFERENCE/SRST_B: R4.1, SW1.1
/PINOUT/BT_1: R50.2, U1.F4
/PINOUT/BT_2: R52.2, U1.H3
/PINOUT/BT_3: R54.2, U1.G4
/PINOUT/BT_4: R56.2, U1.H4
/PINOUT/BT_5: R58.2, U1.G2
/PINOUT/LED_1: R36.2, U1.K3
/PINOUT/LED_2: R42.2, U1.K4
/PINOUT/LED_3: R47.2, U1.J2
/PINOUT/LED_4: R51.2, U1.J3
/PINOUT/LED_5: R57.2, U1.L3
/PINOUT/SW_1: R37.2, SW3.1, U1.H2
/PINOUT/SW_2: R39.2, SW4.1, U1.H5
/PINOUT/SW_3: R41.2, SW5.1, U1.J5
/PINOUT/SW_4: R44.2, SW6.1, U1.J1
/PINOUT/SW_5: R46.2, SW7.1, U1.K1
GND: C1.2, C2.1, C3.2, C4.2, C5.2, C6.2, C7.2, C8.2, C9.2, C10.2, C11.2, C12.2, C13.2, C14.2, C15.2, C16.2, C17.2, C18.1, C19.2, C20.1, C21.2, C22.2, C27.1, C28.2, C29.2, C30.2, C31.1, C32.2, C33.2, C34.2, C35.1, C36.2, C37.1, J1.5, J1.6, J2.5, Q1.2, Q2.2, Q3.2, Q4.2, Q5.2, Q6.2, Q7.2, Q8.2, Q9.2, R7.1, R8.2, R13.1, R15.2, R28.2, R30.1, R32.2, R34.2, R38.2, R43.2, R48.2, R50.1, R52.1, R53.2, R54.1, R56.1, R58.1, R59.2, R62.2, R65.1, R66.2, R67.2, SW1.2, SW3.2, SW4.2, SW5.2, SW6.2, SW7.2, U1.A1, U1.A5, U1.A10, U1.A15, U1.A18, U1.A22, U1.AA10, U1.AA15, U1.AA20, U1.AB1, U1.AB3, U1.AB8, U1.AB13, U1.AB22, U1.B13, U1.B20, U1.C1, U1.C6, U1.C18, U1.C21, U1.C22, U1.D4, U1.D9, U1.D20, U1.E2, U1.E12, U1.E17, U1.E18, U1.E21, U1.E22, U1.F5, U1.F15, U1.F20, U1.G8, U1.G18, U1.G21, U1.G22, U1.H1, U1.H6, U1.H9, U1.H11, U1.H17, U1.H20, U1.J4, U1.J8, U1.J10, U1.J14, U1.J18, U1.J21, U1.J22, U1.K7, U1.K11, U1.K17, U1.K20, U1.L5, U1.L8, U1.L15, U1.L18, U1.L21, U1.L22, U1.M3, U1.M11, U1.M13, U1.M18, U1.M19, U1.N1, U1.N6, U1.N8, U1.N15, U1.N16, U1.N20, U1.N21, U1.N22, U1.P7, U1.P9, U1.P11, U1.P14, U1.R2, U1.R8, U1.R10, U1.R12, U1.R17, U1.R22, U1.T5, U1.T11, U1.T15, U1.U3, U1.U8, U1.U13, U1.U18, U1.V1, U1.V11, U1.W4, U1.W9, U1.W14, U1.W19, U1.Y2, U1.Y7, U1.Y12, U2.B2, U2.B3, U2.B9, U2.D1, U2.E1, U2.E9, U2.G7, U2.G8, U2.J1, U2.J9, U2.K1, U2.K9, U2.L1, U2.L9, U2.M9, U2.N1, U2.N9, U2.R1, U2.T1, U2.T9, U3.1, U3.5, U3.10, U3.11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
unnamed: C1.1, C5.1, U3.9
unnamed: C2.2, J1.1
unnamed: C3.1, C6.1, U3.4
unnamed: C4.1, U3.2, Y1.1
unnamed: C7.1, U3.3, Y1.2
unnamed: C23.1, U11.6
unnamed: C23.2, L6.1, U11.2
unnamed: C24.1, L3.1, U8.2
unnamed: C24.2, U8.6
unnamed: C25.1, L4.1, U9.2
unnamed: C25.2, U9.6
unnamed: C26.1, L5.1, U10.2
unnamed: C26.2, U10.6
unnamed: C35.2, R61.2, U12.7
unnamed: C36.1, R63.1, U12.6
unnamed: C37.2, U2.M1
unnamed: D1.1, R7.2
unnamed: D2.1, R13.2
unnamed: J1.2, U3.7
unnamed: J1.3, U3.8
unnamed: Q1.1, R20.1
unnamed: Q1.3, Q4.1, R21.1
unnamed: Q2.3, Q3.1, R22.2
unnamed: Q3.3, R24.2, U8.5
unnamed: Q4.3, R26.1, U10.5
unnamed: Q5.1, R36.1, R38.1
unnamed: Q5.3, R40.2
unnamed: Q6.1, R42.1, R43.1
unnamed: Q6.3, R45.2
unnamed: Q7.1, R47.1, R48.1
unnamed: Q7.3, R49.2
unnamed: Q8.1, R51.1, R53.1
unnamed: Q8.3, R55.2
unnamed: Q9.1, R57.1, R59.1
unnamed: Q9.3, R60.2
unnamed: R5.2, R6.2, U4.4
unnamed: R8.1, U3.6
unnamed: R11.1, U3.14
unnamed: R14.2, R15.1
unnamed: R16.1, U6.C2
unnamed: R19.2, X1.1
unnamed: R23.1, U11.5
unnamed: R25.2, U9.5
unnamed: R27.2, R28.1, U8.4
unnamed: R29.1, R30.2, U9.4
unnamed: R31.2, R32.1, U10.4
unnamed: R33.2, R34.1, U11.4
unnamed: R61.1, R62.1, U12.8
unnamed: R63.2, U12.9
unnamed: R66.1, U2.F9
unnamed: R67.1, U1.T19
unnamed: U7.A2, U7.A3, U7.A4, U7.A5, U7.B1, U7.B5, U7.C1, U7.C3, U7.C5, U7.D1, U7.D5, U7.E1, U7.E2, U7.E3, U7.E5
VIN: C19.1, C20.2, C21.1, C22.1, R21.2, R22.1, R23.2, R24.1, R26.2, U8.3, U9.3, U10.3, U11.3

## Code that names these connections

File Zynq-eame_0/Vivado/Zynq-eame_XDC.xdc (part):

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
#Buttons

#set_property -dict { PACKAGE_PIN H18    IOSTANDARD LVCMOS33 } [get_ports BT_1]; # button 1
#set_property -dict { PACKAGE_PIN F19    IOSTANDARD LVCMOS33 } [get_ports BT_2]; # button 2
#set_property -dict { PACKAGE_PIN F20    IOSTANDARD LVCMOS33 } [get_ports BT_3]; # button 3
#set_property -dict { PACKAGE_PIN G17    IOSTANDARD LVCMOS33 } [get_ports BT_4]; # button 4
#set_property -dict { PACKAGE_PIN G18    IOSTANDARD LVCMOS33 } [get_ports BT_5]; # button 5

#Leds

#set_property -dict { PACKAGE_PIN L20    IOSTANDARD LVCMOS33 } [get_ports LED_1]; # Led 1
#set_property -dict { PACKAGE_PIN K19    IOSTANDARD LVCMOS33 } [get_ports LED_2]; # Led 2
#set_property -dict { PACKAGE_PIN J19    IOSTANDARD LVCMOS33 } [get_ports LED_3]; # Led 3
#set_property -dict { PACKAGE_PIN L16    IOSTANDARD LVCMOS33 } [get_ports LED_4]; # Led 4
#set_property -dict { PACKAGE_PIN L17    IOSTANDARD LVCMOS33 } [get_ports LED_5]; # Led 5

#Switchs

#set_property -dict { PACKAGE_PIN K17    IOSTANDARD LVCMOS33 } [get_ports SW_1]; # Switch 1
#set_property -dict { PACKAGE_PIN K18    IOSTANDARD LVCMOS33 } [get_ports SW_2]; # Switch 2
#set_property -dict { PACKAGE_PIN H16    IOSTANDARD LVCMOS33 } [get_ports SW_3]; # Switch 3
#set_property -dict { PACKAGE_PIN H17    IOSTANDARD LVCMOS33 } [get_ports SW_4]; # Switch 4
#set_property -dict { PACKAGE_PIN J18    IOSTANDARD LVCMOS33 } [get_ports SW_5]; # Switch 5

#SD

#set_property -dict { PACKAGE_PIN D14    IOSTANDARD LVCMOS33 } [get_ports SD_CLK]; # SD_CLK
#set_property -dict { PACKAGE_PIN C17    IOSTANDARD LVCMOS33 } [get_ports SD_CMD]; # SD_CMD
#set_property -dict { PACKAGE_PIN E12    IOSTANDARD LVCMOS33 } [get_ports SD_D0]; # SD_D0
#set_property -dict { PACKAGE_PIN A9     IOSTANDARD LVCMOS33 } [get_ports SD_D1]; # SD_D1
#set_property -dict { PACKAGE_PIN F13    IOSTANDARD LVCMOS33 } [get_ports SD_D2]; # SD_D2
#set_property -dict { PACKAGE_PIN B15    IOSTANDARD LVCMOS33 } [get_ports SD_D3]; # SD_D3

#USB RX - TX

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
#QUAD-SPI FLASH MEMORY

#set_property -dict { PACKAGE_PIN A7    IOSTANDARD LVCMOS33 } [get_ports MIO1]; # CS#
#set_property -dict { PACKAGE_PIN B8    IOSTANDARD LVCMOS33 } [get_ports MIO2]; # IO0
#set_property -dict { PACKAGE_PIN D6    IOSTANDARD LVCMOS33 } [get_ports MIO3]; # IO1
#set_property -dict { PACKAGE_PIN B7    IOSTANDARD LVCMOS33 } [get_ports MIO4]; # IO2
#set_property -dict { PACKAGE_PIN A6    IOSTANDARD LVCMOS33 } [get_ports MIO5]; # IO3
#set_property -dict { PACKAGE_PIN A5    IOSTANDARD LVCMOS33 } [get_ports MIO6]; # SCK


# Pin Bank 34
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#MIO Pins
#JP3

#set_property -dict { PACKAGE_PIN E6    IOSTANDARD LVCMOS33 } [get_ports Pin1]; # pin 1 - MIO_0
#set_property -dict { PACKAGE_PIN D8    IOSTANDARD LVCMOS33 } [get_ports Pin2]; # pin 2 - MIO_7
#set_property -dict { PACKAGE_PIN D5    IOSTANDARD LVCMOS33 } [get_ports Pin3]; # pin 3 - MIO_8
#set_property -dict { PACKAGE_PIN B5    IOSTANDARD LVCMOS33 } [get_ports Pin4]; # pin 4 - MIO_9
#set_property -dict { PACKAGE_PIN E9    IOSTANDARD LVCMOS33 } [get_ports Pin5]; # pin 5 - MIO_10
#set_property -dict { PACKAGE_PIN C6    IOSTANDARD LVCMOS33 } [get_ports Pin6]; # pin 6 - MIO_11
#set_property -dict { PACKAGE_PIN D9    IOSTANDARD LVCMOS33 } [get_ports Pin7]; # pin 7 - MIO_12
#set_property -dict { PACKAGE_PIN E8    IOSTANDARD LVCMOS33 } [get_ports Pin8]; # pin 8 - MIO_13
#set_property -dict { PACKAGE_PIN C5    IOSTANDARD LVCMOS33 } [get_ports Pin9]; # pin 9 - MIO_14
#set_property -dict { PACKAGE_PIN C8    IOSTANDARD LVCMOS33 } [get_ports Pin10]; # pin 10 - MIO_15
#set_property -dict { PACKAGE_PIN A19    IOSTANDARD LVCMOS33 } [get_ports Pin11]; # pin 11 - MIO_16
#set_property -dict { PACKAGE_PIN E14    IOSTANDARD LVCMOS33 } [get_ports Pin12]; # pin 12 - MIO_17
#set_property -dict { PACKAGE_PIN B18    IOSTANDARD LVCMOS33 } [get_ports Pin13]; # pin 13 - MIO_18
#set_property -dict { PACKAGE_PIN D10    IOSTANDARD LVCMOS33 } [get_ports Pin14]; # pin 14 - MIO_19
#set_property -dict { PACKAGE_PIN A17    IOSTANDARD LVCMOS33 } [get_ports Pin15]; # pin 15 - MIO_20
#set_property -dict { PACKAGE_PIN F14    IOSTANDARD LVCMOS33 } [get_ports Pin16]; # pin 16 - MIO_21
#set_property -dict { PACKAGE_PIN B17    IOSTANDARD LVCMOS33 } [get_ports Pin17]; # pin 17 - MIO_22
#set_property -dict { PACKAGE_PIN D11    IOSTANDARD LVCMOS33 } [get_ports Pin18]; # pin 18 - MIO_23
#set_property -dict { PACKAGE_PIN A15    IOSTANDARD LVCMOS33 } [get_ports Pin19]; # pin 19 - MIO_26
#set_property -dict { PACKAGE_PIN D13    IOSTANDARD LVCMOS33 } [get_ports Pin20]; # pin 20 - MIO_27
#set_property -dict { PACKAGE_PIN C16    IOSTANDARD LVCMOS33 } [get_ports Pin21]; # pin 21 - MIO_28
#set_property -dict { PACKAGE_PIN C13    IOSTANDARD LVCMOS33 } [get_ports Pin22]; # pin 22 - MIO_29
#set_property -dict { PACKAGE_PIN C15    IOSTANDARD LVCMOS33 } [get_ports Pin23]; # pin 23 - MIO_30
#set_property -dict { PACKAGE_PIN E16    IOSTANDARD LVCMOS33 } [get_ports Pin24]; # pin 24 - MIO_31
#set_property -dict { PACKAGE_PIN A14    IOSTANDARD LVCMOS33 } [get_ports Pin25]; # pin 25 - MIO_32
#set_property -dict { PACKAGE_PIN D15    IOSTANDARD LVCMOS33 } [get_ports Pin26]; # pin 26 - MIO_33
#set_property -dict { PACKAGE_PIN A12    IOSTANDARD LVCMOS33 } [get_ports Pin27]; # pin 27 - MIO_34
#set_property -dict { PACKAGE_PIN F12    IOSTANDARD LVCMOS33 } [get_ports Pin28]; # pin 28 - MIO_35
#set_property -dict { PACKAGE_PIN E13    IOSTANDARD LVCMOS33 } [get_ports Pin29]; # pin 29 - MIO_38
#set_property -dict { PACKAGE_PIN C18    IOSTANDARD LVCMOS33 } [get_ports Pin30]; # pin 30 - MIO_39
#set_property -dict { PACKAGE_PIN D16    IOSTANDARD LVCMOS33 } [get_ports Pin31]; # pin 31 - MIO_46
#set_property -dict { PACKAGE_PIN B14    IOSTANDARD LVCMOS33 } [get_ports Pin32]; # pin 32 - MIO_47
#set_property -dict { PACKAGE_PIN B12    IOSTANDARD LVCMOS33 } [get_ports Pin33]; # pin 33 - MIO_48
#set_property -dict { PACKAGE_PIN C12    IOSTANDARD LVCMOS33 } [get_ports Pin34]; # pin 34 - MIO_49
#set_property -dict { PACKAGE_PIN B13    IOSTANDARD LVCMOS33 } [get_ports Pin35]; # pin 35 - MIO_50
#set_property -dict { PACKAGE_PIN B9     IOSTANDARD LVCMOS33 } [get_ports Pin36]; # pin 36 - MIO_51
#set_property -dict { PACKAGE_PIN C10    IOSTANDARD LVCMOS33 } [get_ports Pin37]; # pin 37 - MIO_52
#set_property -dict { PACKAGE_PIN C11    IOSTANDARD LVCMOS33 } [get_ports Pin38]; # pin 38 - MIO_53



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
